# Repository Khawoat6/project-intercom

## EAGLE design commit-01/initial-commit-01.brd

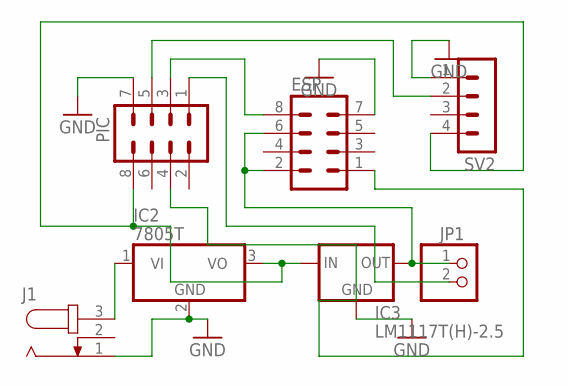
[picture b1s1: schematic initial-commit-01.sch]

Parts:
ESP: MA04-2
IC2: 7805T; TO220H
IC3: LM1117T(H)-2.5; TO220H
J1: JACK-PLUG1; SPC4078
JP1: PINHD-1X2; 1X02
PIC: MA04-2
SV2: MA04-1

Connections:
GND: ESP.7, IC2.2 (GND), IC3.1 (GND), J1.1, PIC.7, SV2.1
unnamed: IC2.1 (VI), J1.3
unnamed: ESP.1, PIC.4
unnamed: ESP.2, ESP.6, IC3.2 (OUT), JP1.1
unnamed: ESP.8, PIC.3
unnamed: JP1.2, PIC.1
unnamed: PIC.5, SV2.2
unnamed: IC2.3 (VO), IC3.3 (IN), PIC.8, SV2.4

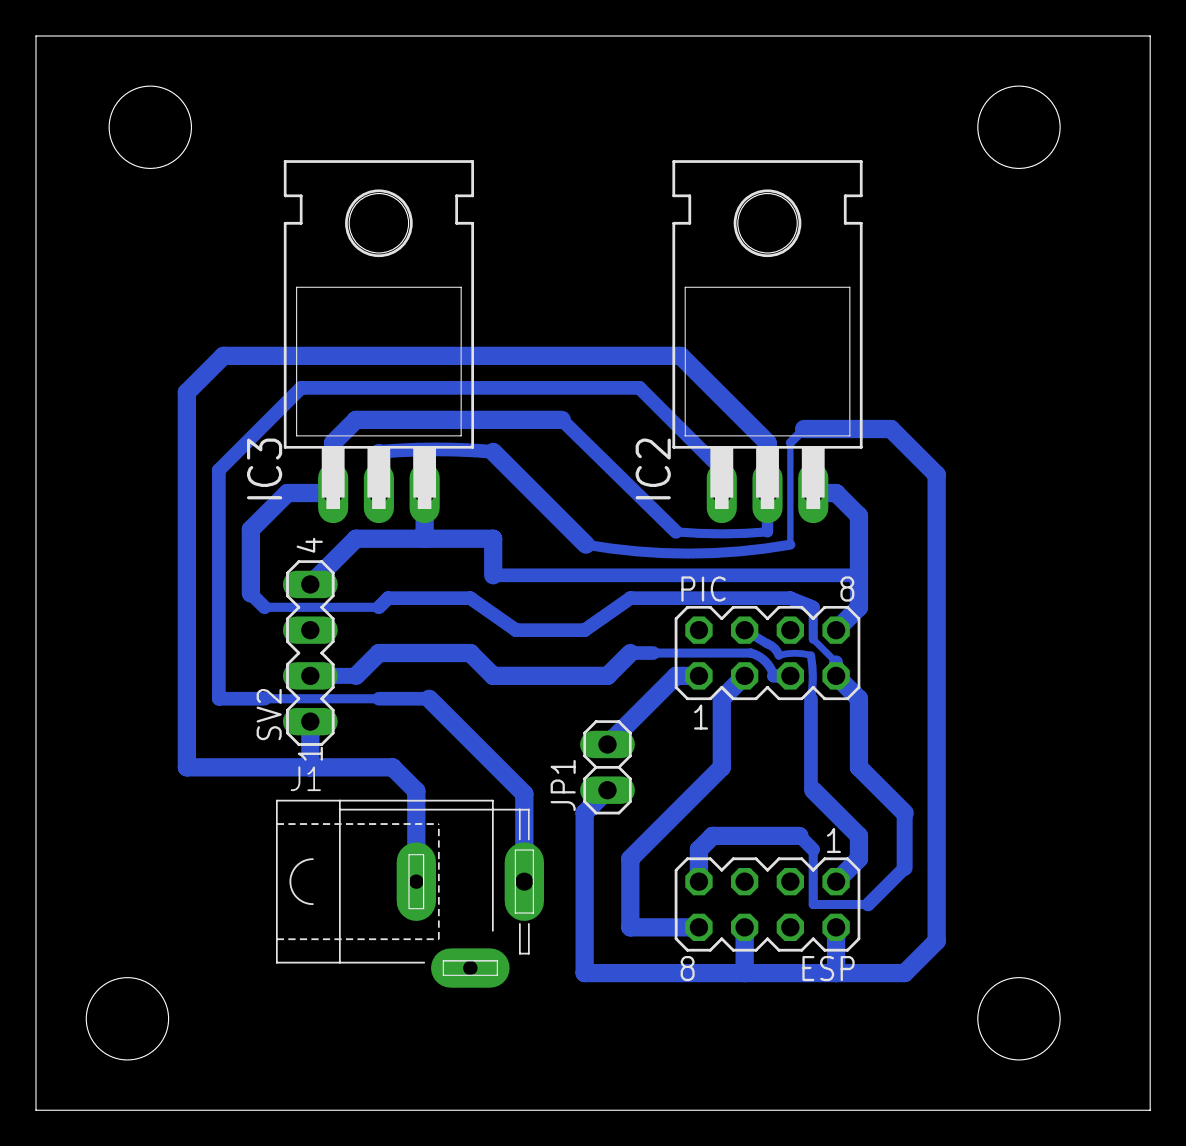
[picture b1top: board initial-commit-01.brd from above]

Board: 2 copper layers, 61.9 x 59.7 mm, 7 parts (0 on the bottom side), 8 nets.

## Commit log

2018-11-27 :tada: Initial commit N0.1
2018-11-27 :hammer: edit file test01 and test02
2018-11-27 :hammer: add folder images
